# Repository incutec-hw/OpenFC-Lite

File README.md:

# OpenFC-Lite

Open-source Betaflight flight controller built on the RP2354B — 6-layer, 30.5×30.5 mm mounting, 3S–6S input, microSD blackbox, analog OSD.

Motor outputs are signal-level lines that drive an external 4-in-1 ESC (e.g. OpenESC) over the 8-pin ESC connector — there are no onboard motor drivers. Barometer, integrated receiver, and onboard SPI blackbox flash are omitted by design; blackbox logging uses the microSD slot, and the receiver connects externally over UART.

> A smaller **[OpenFC-Lite-Mini](https://github.com/incutec-hw/OpenFC-Lite-Mini)** (20×20 mm, RP2354A) shares this design. **Both are being ordered for Rev 2;** this full-size board adds bigger pads, more I/O, full-size SD, and OSD debug pads.

## Specifications

| | |
|---|---|
| **MCU** | RP2354B — dual-core ARM Cortex-M33, QFN-80, integrated stacked flash (U2, LCSC C39843328) |
| **IMU** | 6-axis MEMS on SPI0, LGA-14 footprint. Rev 1 populates LSM6DSV16XTR (U9). The footprint also accepts TDK ICM-426xx/456xx — IMU is a population choice, not a layout change |
| **Barometer** | None (omitted by design) |
| **Blackbox** | microSD card slot (push-push, TF-021B-H265 family) on SPI1 |
| **OSD** | Analog, PIO-driven: sync-separator comparator + video op-amp + SPDT analog switch (no MAX7456-class OSD chip, no onboard flash). Includes OSD debug/bring-up pads (not on the Mini). |
| **Regulators** | 10V switchable buck, 5V always-on buck, USB/BATT power mux, 3.3V LDO, 1.8V gyro LDO (see power tree) |
| **UARTs** | 4 total — 2 hardware UARTs + 2 PIO software UARTs |
| **Motor outputs** | 4 (MOTOR1–MOTOR4), signal-level to external ESC |
| **Battery input** | +BATT, 3S–6S |
| **Copper layers** | 6 |
| **Board size** | 38.9 × 38.9 mm |
| **Mounting** | 30.5 × 30.5 mm pattern, 4× Ø4.0 mm holes |
| **USB** | USB-C (USB full-speed, D+/D- with 30Ω series resistors; configuration/flashing) |

### Power tree

| Rail | Source | Regulator | Notes |
|---|---|---|---|
| +10V (switchable) | +BATT | LMR51430YFDDCR buck (U3) | EN-gated via GPIO (10V_ENABLE). FB divider 100k : 6.49k → ≈9.85V. 4.7µH (L2) / 22µF 16V output. VTX/camera rail. |
| +5V (always-on) | +BATT | LMR51430YFDDCR buck (U4) | 4.7µH (L3). |
| +5V (muxed) | +5V_BUCK + +5V_USB | TPS2116DRLR (U5) | Auto-selects battery vs USB source. |
| +3.3V | +5V | LP5912-3.3DRVR (U7) | Logic LDO. |
| +1.8V_GYRO | +5V | NCV8187AMT180TAG (U6) | 1.2 A LDO, high PSRR (80 dB to 10 kHz). Dedicated IMU analog supply. |
| +1.1V | +3.3V | RP2354B internal core regulator | MCU core. |

## Connectivity / IO

**Serial**
- UART0 (UART0_TX / UART0_RX) — hardware UART
- UART1 (UART1_TX / UART1_RX) — hardware UART
- PIO UART0 (PIOUART0_TX / PIOUART0_RX) — software UART via PIO
- PIO UART1 (PIOUART1_TX / PIOUART1_RX) — software UART via PIO

**Buses**
- I2C0 (SCL / SDA) — exposed on expansion pads
- SPI0 (SCK / MOSI / MISO, + GYRO_INT) — IMU
- SPI1 (SCK / MOSI / MISO) — microSD blackbox

**Motor / actuator**
- MOTOR1, MOTOR2, MOTOR3, MOTOR4 — to external ESC
- LED_STRIP — addressable LED output
- BEEPER / BUZZER- — N-MOS-driven buzzer output

**Analog inputs (each via RC filter)**
- ADC_VBAT — battery voltage sense (resistive divider)
- ESC_CURRENT — current sense from ESC
- RSSI — analog RSSI

**OSD (analog video chain)**
- OSD_SYNC, OSD_EN, OSD_W, OSD_LVL — composite-video sync/overlay signals to the OSD front-end

**Status / control**
- LED0 — status LED
- 10V_ENABLE — switches the 10V VTX/camera rail

### Connectors

| Ref | Part | Type | Function |
|---|---|---|---|
| U8 | SM06B-SRSS-TB | 6-pin SMD JST SH | Digital VTX |
| P1 | SM08B-SRSS-TB | 8-pin TH JST SH | ESC harness |
| USB1 | Type-C 16P | USB-C | Configuration / flashing |

A large number of through-hole solder pads (J*) expose rails and signal lines (5V, GND, MOTOR1–4, UART, LED_STRIP, RSSI, etc.) for direct wiring.

## Repository structure

```
OpenFC-Lite/
├── README.md
├── LICENSE                       CERN-OHL-S-2.0
├── CLAUDE.md                     project working agreement / design notes
├── hardware/                     KiCad 9 project (single project)
│   ├── OpenFC.kicad_pro          project file
│   ├── OpenFC.kicad_sch          top-level (hierarchical) schematic
│   ├── rp2350a.kicad_sch         RP2354B MCU + support
│   ├── power.kicad_sch           regulators (10V/5V bucks, mux, 3.3V/1.8V LDOs)
│   ├── imu.kicad_sch             6-axis IMU on SPI0
│   ├── osd.kicad_sch             analog OSD chain
│   ├── blackbox.kicad_sch        microSD card slot on SPI1
│   ├── pads.kicad_sch            solder pads and connectors
│   ├── OpenFC.kicad_pcb          PCB layout (6 layers)
│   ├── OpenFC.kicad_dru          custom design rules
│   ├── lib.kicad_sym             project-local symbol library
│   ├── lib.3dshapes/             project-local 3D models
│   ├── datasheets/               component datasheets
│   ├── production/               JLCPCB exports (rev1: gerbers zip, BOM, CPL)
│   └── tools/                    read-only analysis scripts (kicad-skip / pcbnew)
├── analysis/                     netlist/IC/power extraction output
└── images/                       board renders
```

All symbol, footprint, and 3D-model libraries are project-local — no external library setup required to open the project.

## Firmware

Target firmware is **Betaflight** on the RP2350 (PICO) platform. The RP2354B uses the Raspberry Pi Pico SDK (C/C++). PIO blocks drive the DShot motor outputs, the software UARTs, the LED strip, and the analog-OSD pixel timing.

Note: the RP2350 analog-OSD (FB_OSD) driver is still an open upstream Betaflight PR stack — OSD is not yet flyable from an upstream binary. See the [Wiki](https://github.com/incutec-hw/OpenFC-Lite/wiki) for bring-up status.

## License

Hardware licensed under [CERN-OHL-S-2.0](https://ohwr.org/cern_ohl_s_v2.txt). See [LICENSE](LICENSE).

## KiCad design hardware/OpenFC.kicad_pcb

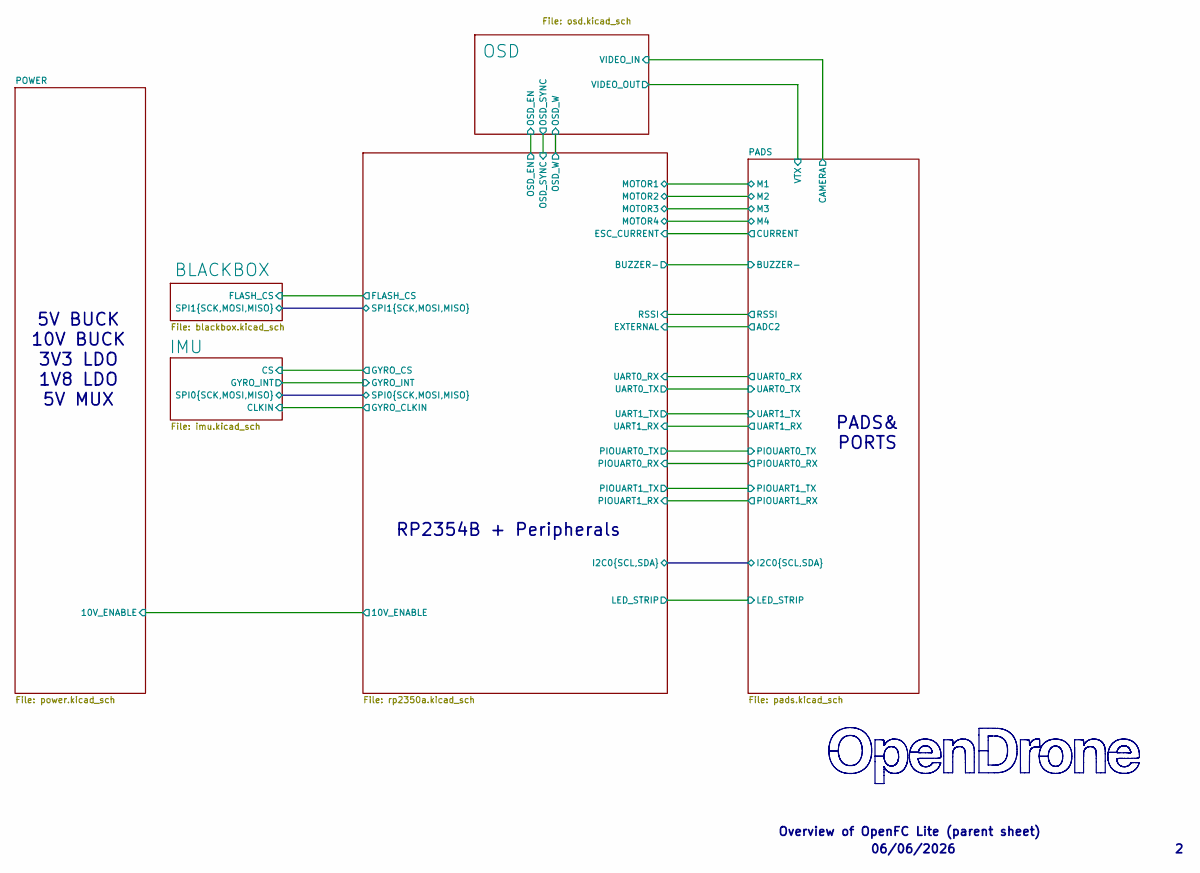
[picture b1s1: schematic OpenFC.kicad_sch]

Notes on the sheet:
Overview of OpenFC Lite (parent sheet)
5V BUCK 10V BUCK 3V3 LDO 1V8 LDO 5V MUX
06/06/2026
RP2354B + Peripherals
PADS& PORTS

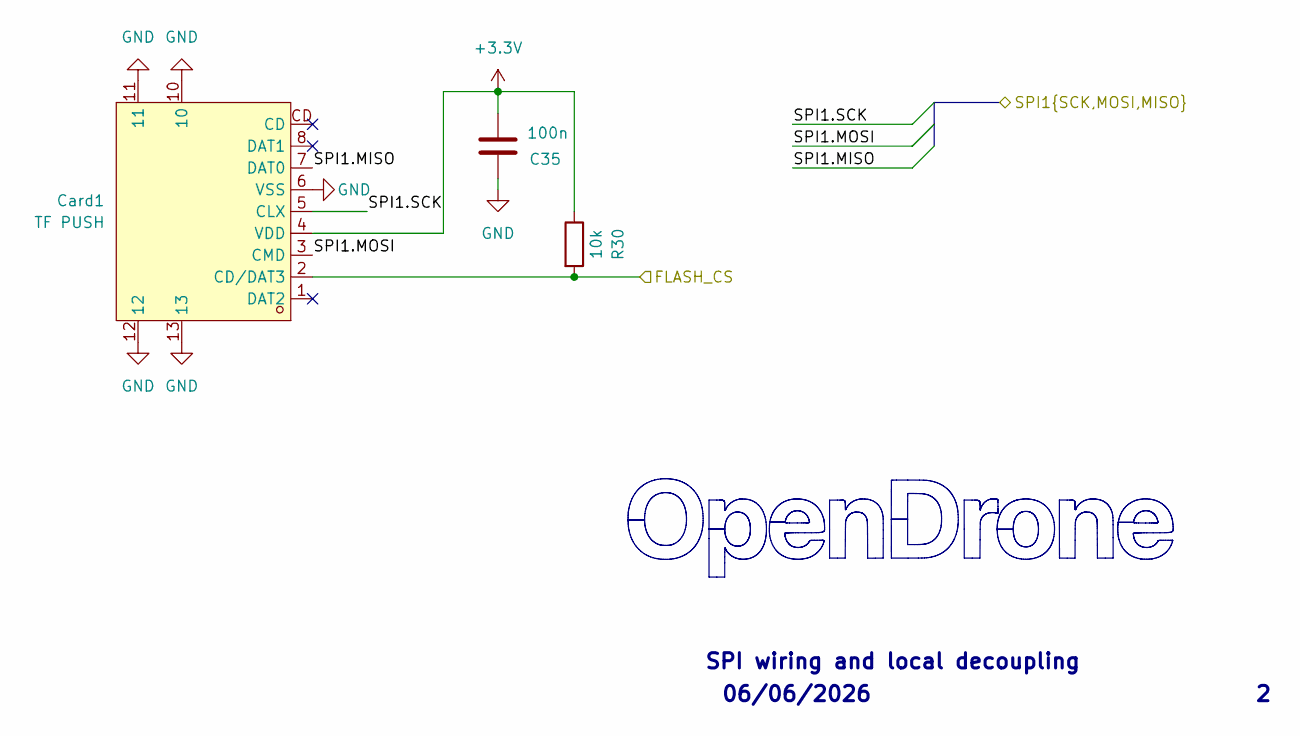
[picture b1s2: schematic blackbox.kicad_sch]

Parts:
C35: 100n; C_0201_0603Metric; MPN GRM033R61E104KE14D; LCSC C76939
Card1: TF PUSH; TF-SMD_TF-PUSH; MPN TF PUSH; LCSC C393941
R30: 10k; R_0201_0603Metric; MPN RC0201FR-0710KL; LCSC C106225

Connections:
+3.3V: C35.1, Card1.4 (VDD), R30.1; also elsewhere on the board
/BLACKBOX/FLASH_CS: Card1.2 (CD/DAT3), R30.2; also elsewhere on the board
/BLACKBOX/SPI1.MISO: Card1.7 (DAT0); also elsewhere on the board
/BLACKBOX/SPI1.MOSI: Card1.3 (CMD); also elsewhere on the board
/BLACKBOX/SPI1.SCK: Card1.5 (CLX); also elsewhere on the board
GND: C35.2, Card1.6 (VSS), Card1.10, Card1.11, Card1.12, Card1.13; also elsewhere on the board

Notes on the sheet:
SPI wiring and local decoupling
06/06/2026

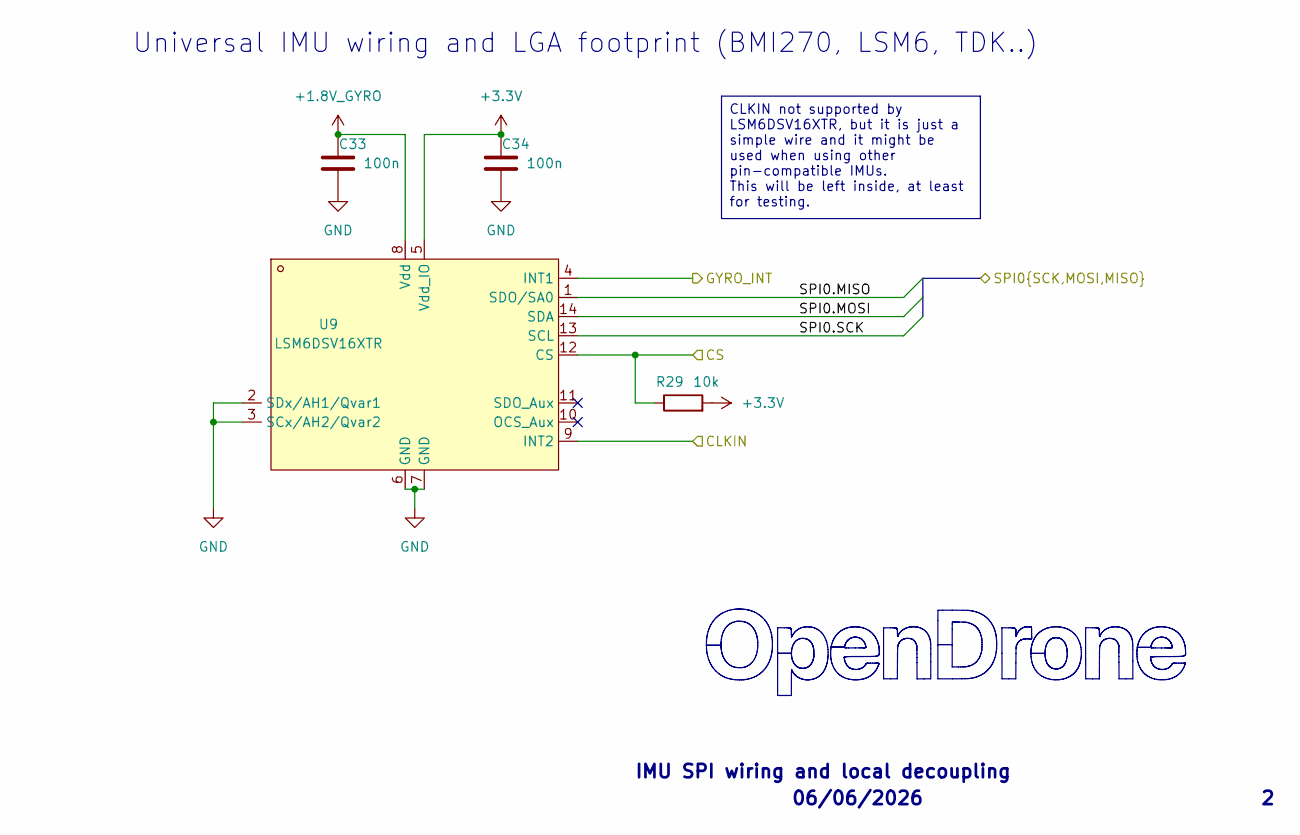
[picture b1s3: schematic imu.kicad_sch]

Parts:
C33, C34: 100n; C_0201_0603Metric; MPN GRM033R61E104KE14D; LCSC C76939
R29: 10k; R_0201_0603Metric; MPN RC0201FR-0710KL; LCSC C106225
U9: LSM6DSV16XTR; LGA-14_L3.0-W2.5-P0.50-BR; MPN LSM6DSV16XTR; LCSC C5267406

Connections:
+1.8V_GYRO: C33.1, U9.8 (Vdd); also elsewhere on the board
+3.3V: C34.1, R29.2, U9.5 (Vdd_IO); also elsewhere on the board
/IMU/CLKIN: U9.9 (INT2); also elsewhere on the board
/IMU/CS: R29.1, U9.12 (CS); also elsewhere on the board
/IMU/GYRO_INT: U9.4 (INT1); also elsewhere on the board
/IMU/SPI0.MISO: U9.1 (SDO/SA0); also elsewhere on the board
/IMU/SPI0.MOSI: U9.14 (SDA); also elsewhere on the board
/IMU/SPI0.SCK: U9.13 (SCL); also elsewhere on the board
GND: C33.2, C34.2, U9.2 (SDx/AH1/Qvar1), U9.3 (SCx/AH2/Qvar2), U9.6 (GND), U9.7 (GND); also elsewhere on the board

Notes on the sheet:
06/06/2026
IMU SPI wiring and local decoupling
Universal IMU wiring and LGA footprint (BMI270, LSM6, TDK..)
CLKIN not supported by LSM6DSV16XTR, but it is just a simple wire and it might be used when using other pin-compatible IMUs. This will be left inside, at least for testing.

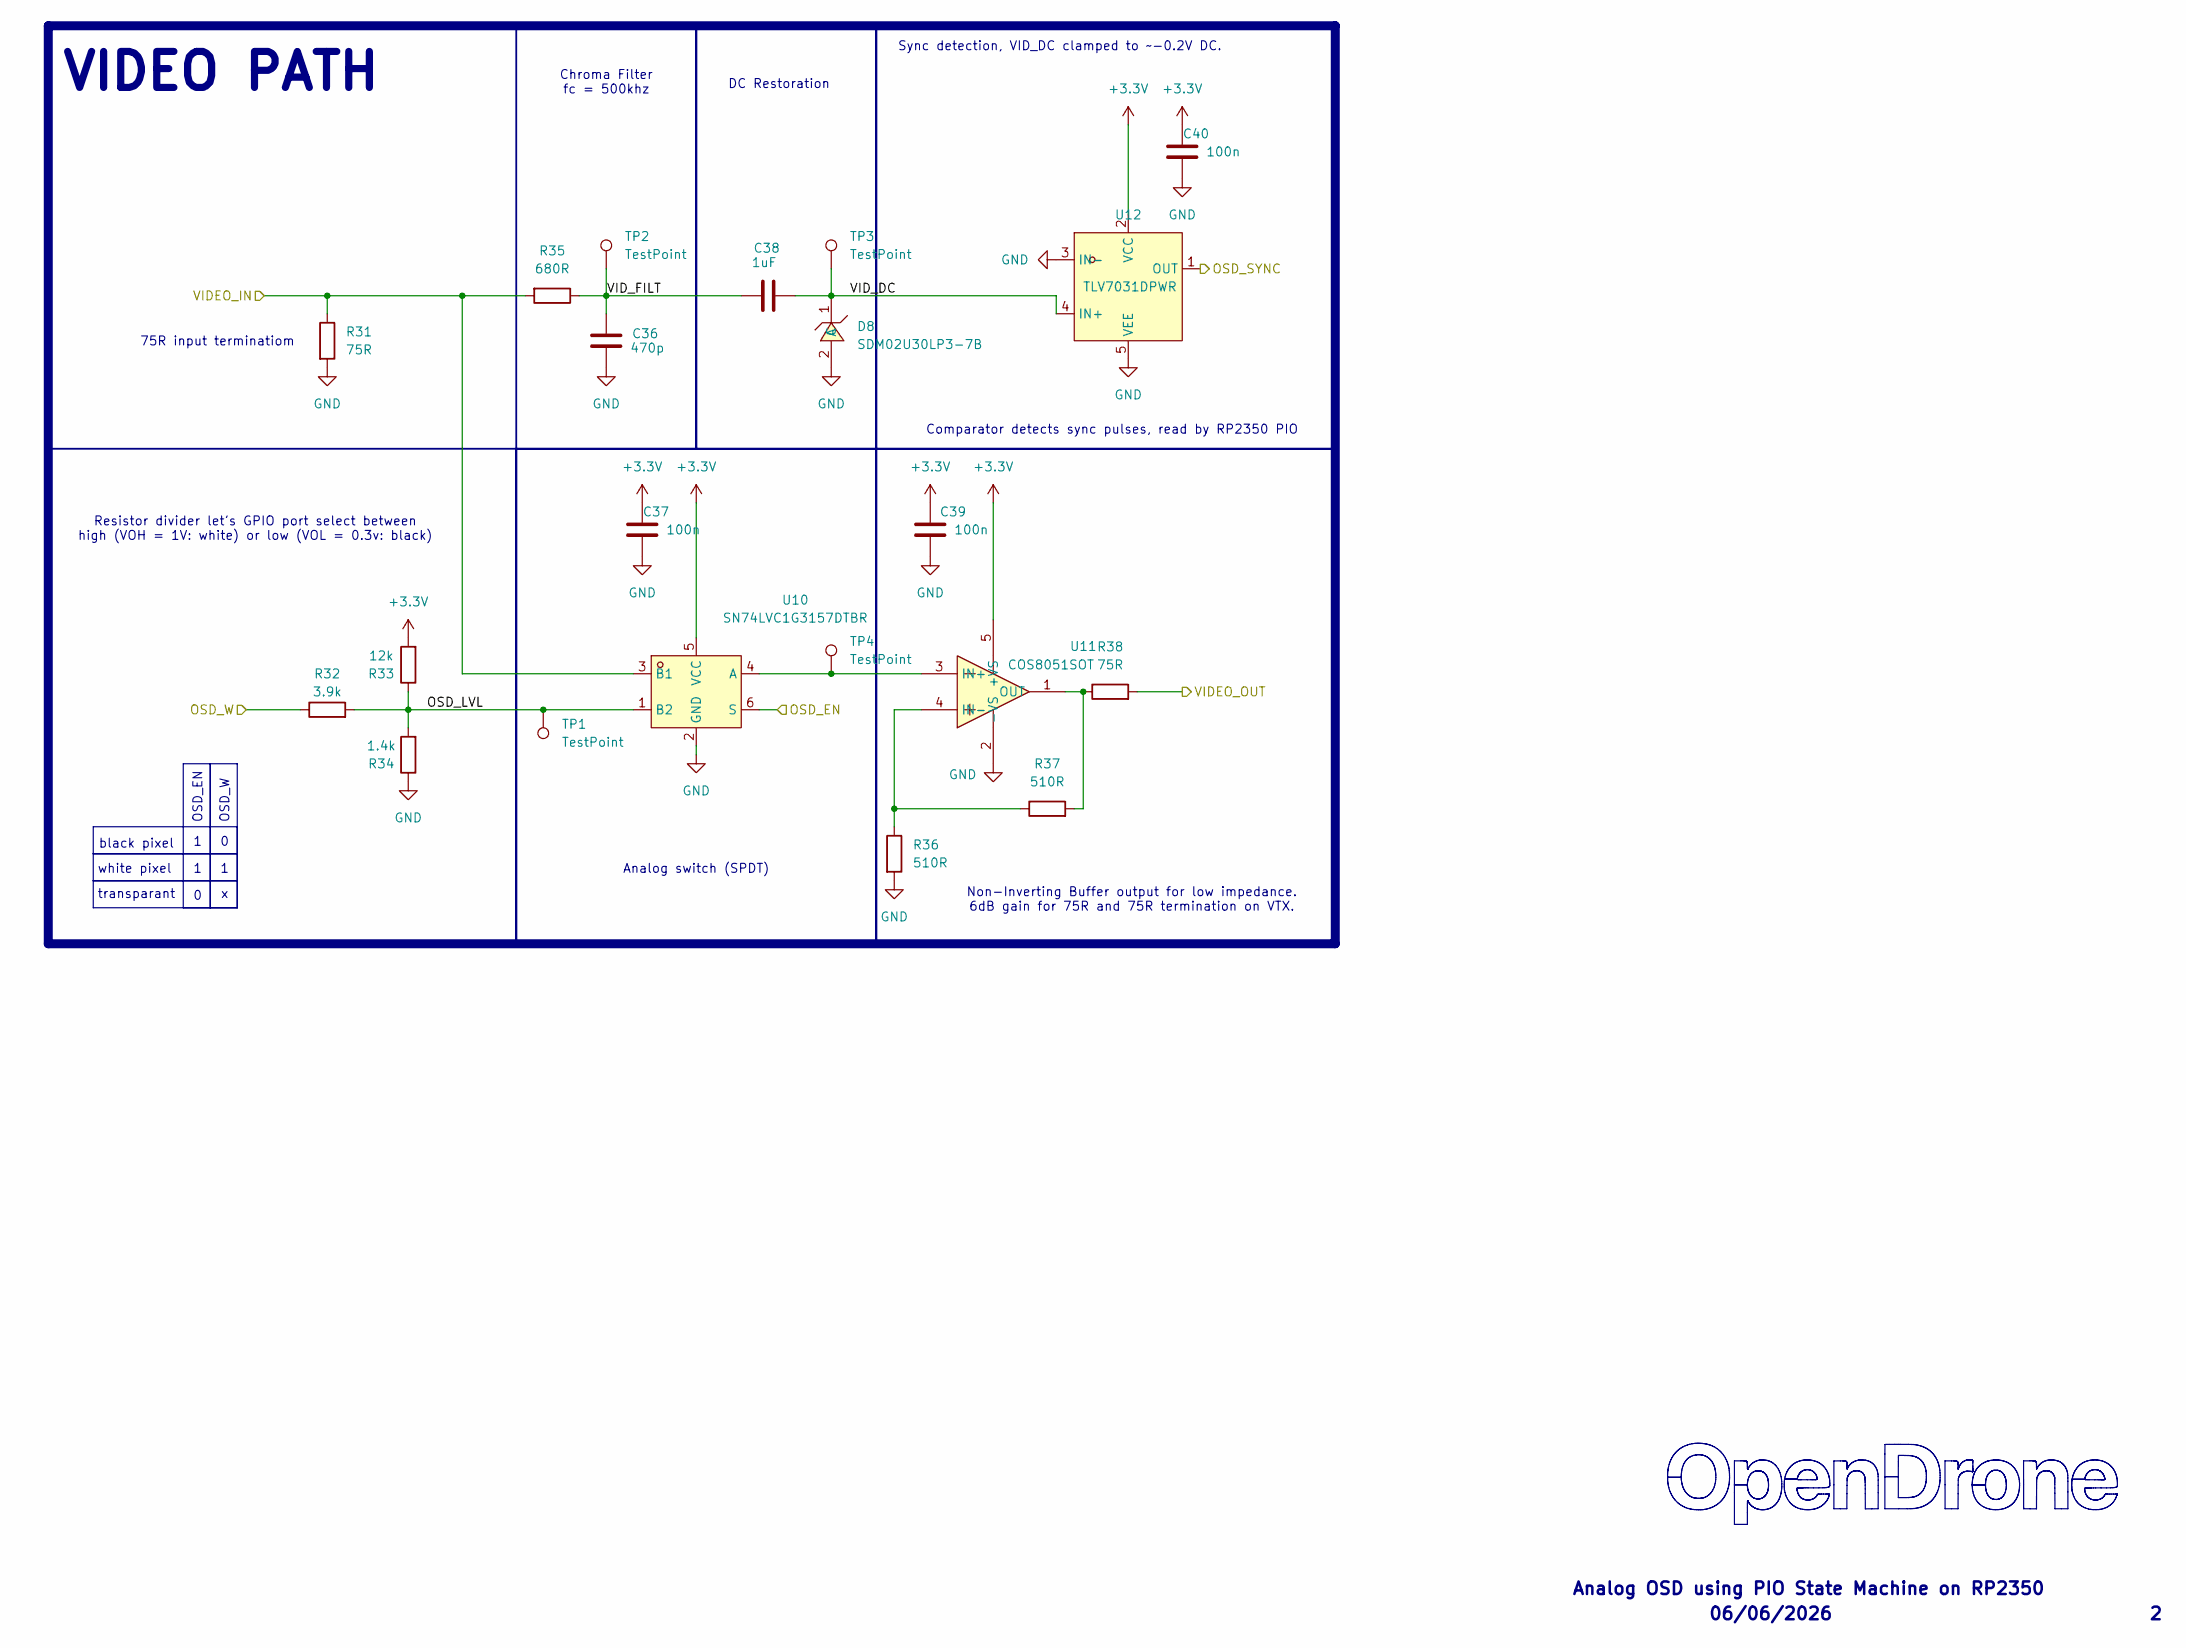
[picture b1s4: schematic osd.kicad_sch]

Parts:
C36: 470p; C_0201_0603Metric; MPN CC0201JRX7R9BB471; LCSC C526944
C37, C39, C40: 100n; C_0201_0603Metric; MPN GRM033R60J104KE19D; LCSC C76928
C38: 1uF; C_0402_1005Metric; MPN CL05A105KA5NQNC; LCSC C52923
D8: SDM02U30LP3-7B; X3-DFN0603-2_L0.6-W0.3-RD; MPN SDM02U30LP3-7B; LCSC C151629
R31, R38: 75R; R_0201_0603Metric; MPN RC0201FR-0775RL; LCSC C274878
R32: 3.9k; R_0201_0603Metric; MPN RC0201FR-073K9L; LCSC C273280
R33: 12k; R_0201_0603Metric; MPN 0201WMF1202TEE; LCSC C270363
R34: 1.4k; R_0201_0603Metric; MPN 0201WMF1401TEE; LCSC C423739
R35: 680R; R_0201_0603Metric; MPN 0201WMF6800TEE; LCSC C473509
R36, R37: 510R; R_0201_0603Metric; LCSC C57784
TP1, TP2, TP3, TP4: TestPoint; TestPoint_Pad_D1.5mm
U10: SN74LVC1G3157DTBR; X2SON-6_L1.0-W0.8-BL; MPN SN74LVC1G3157DTBR; LCSC C2673087
U11: COS8051SOT; SOT-23-5_L3.0-W1.7-P0.95-LS2.8-BR; MPN COS8051SOT; LCSC C7463385
U12: TLV7031DPWR; X2SON-4_L0.8-W0.8-P0.48-TL-A; MPN TLV7031DPWR; LCSC C2876045

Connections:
+3.3V: C37.1, C39.1, C40.1, R33.2, U10.5 (VCC), U11.5 (+VS), U12.2 (VCC); also elsewhere on the board
/OSD/OSD_EN: U10.6 (S); also elsewhere on the board
/OSD/OSD_LVL: R32.2, R33.1, R34.2, TP1.1 (1_1), U10.1 (B2)
/OSD/OSD_SYNC: U12.1 (OUT); also elsewhere on the board
/OSD/OSD_W: R32.1; also elsewhere on the board
/OSD/VIDEO_IN: R31.1, R35.2, U10.3 (B1); also elsewhere on the board
/OSD/VIDEO_OUT: R38.2; also elsewhere on the board
/OSD/VID_DC: C38.2, D8.1 (C), TP3.1 (1_1), U12.4 (IN+)
/OSD/VID_FILT: C36.1, C38.1, R35.1, TP2.1 (1_1)
GND: C36.2, C37.2, C39.2, C40.2, D8.2 (A), R31.2, R34.1, R36.2, U10.2 (GND), U11.2 (-VS), U12.3 (IN-), U12.5 (VEE); also elsewhere on the board
unnamed: TP4.1 (1_1), U10.4 (A), U11.3 (IN+)
unnamed: R36.1, R37.1, U11.4 (IN-)
unnamed: R37.2, R38.1, U11.1 (OUT)

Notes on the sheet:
black pixel
Comparator detects sync pulses, read by RP2350 PIO
06/06/2026
Analog OSD using PIO State Machine on RP2350
Sync detection, VID_DC clamped to ~-0.2V DC.
Non-Inverting Buffer output for low impedance. 6dB gain for 75R and 75R termination on VTX.
white pixel
75R input terminatiom
OSD_W
Chroma Filter fc = 500khz
VIDEO PATH
Analog switch (SPDT)
OSD_EN
transparant
DC Restoration
Resistor divider let's GPIO port select between high (VOH = 1V: white) or low (VOL = 0.3v: black)

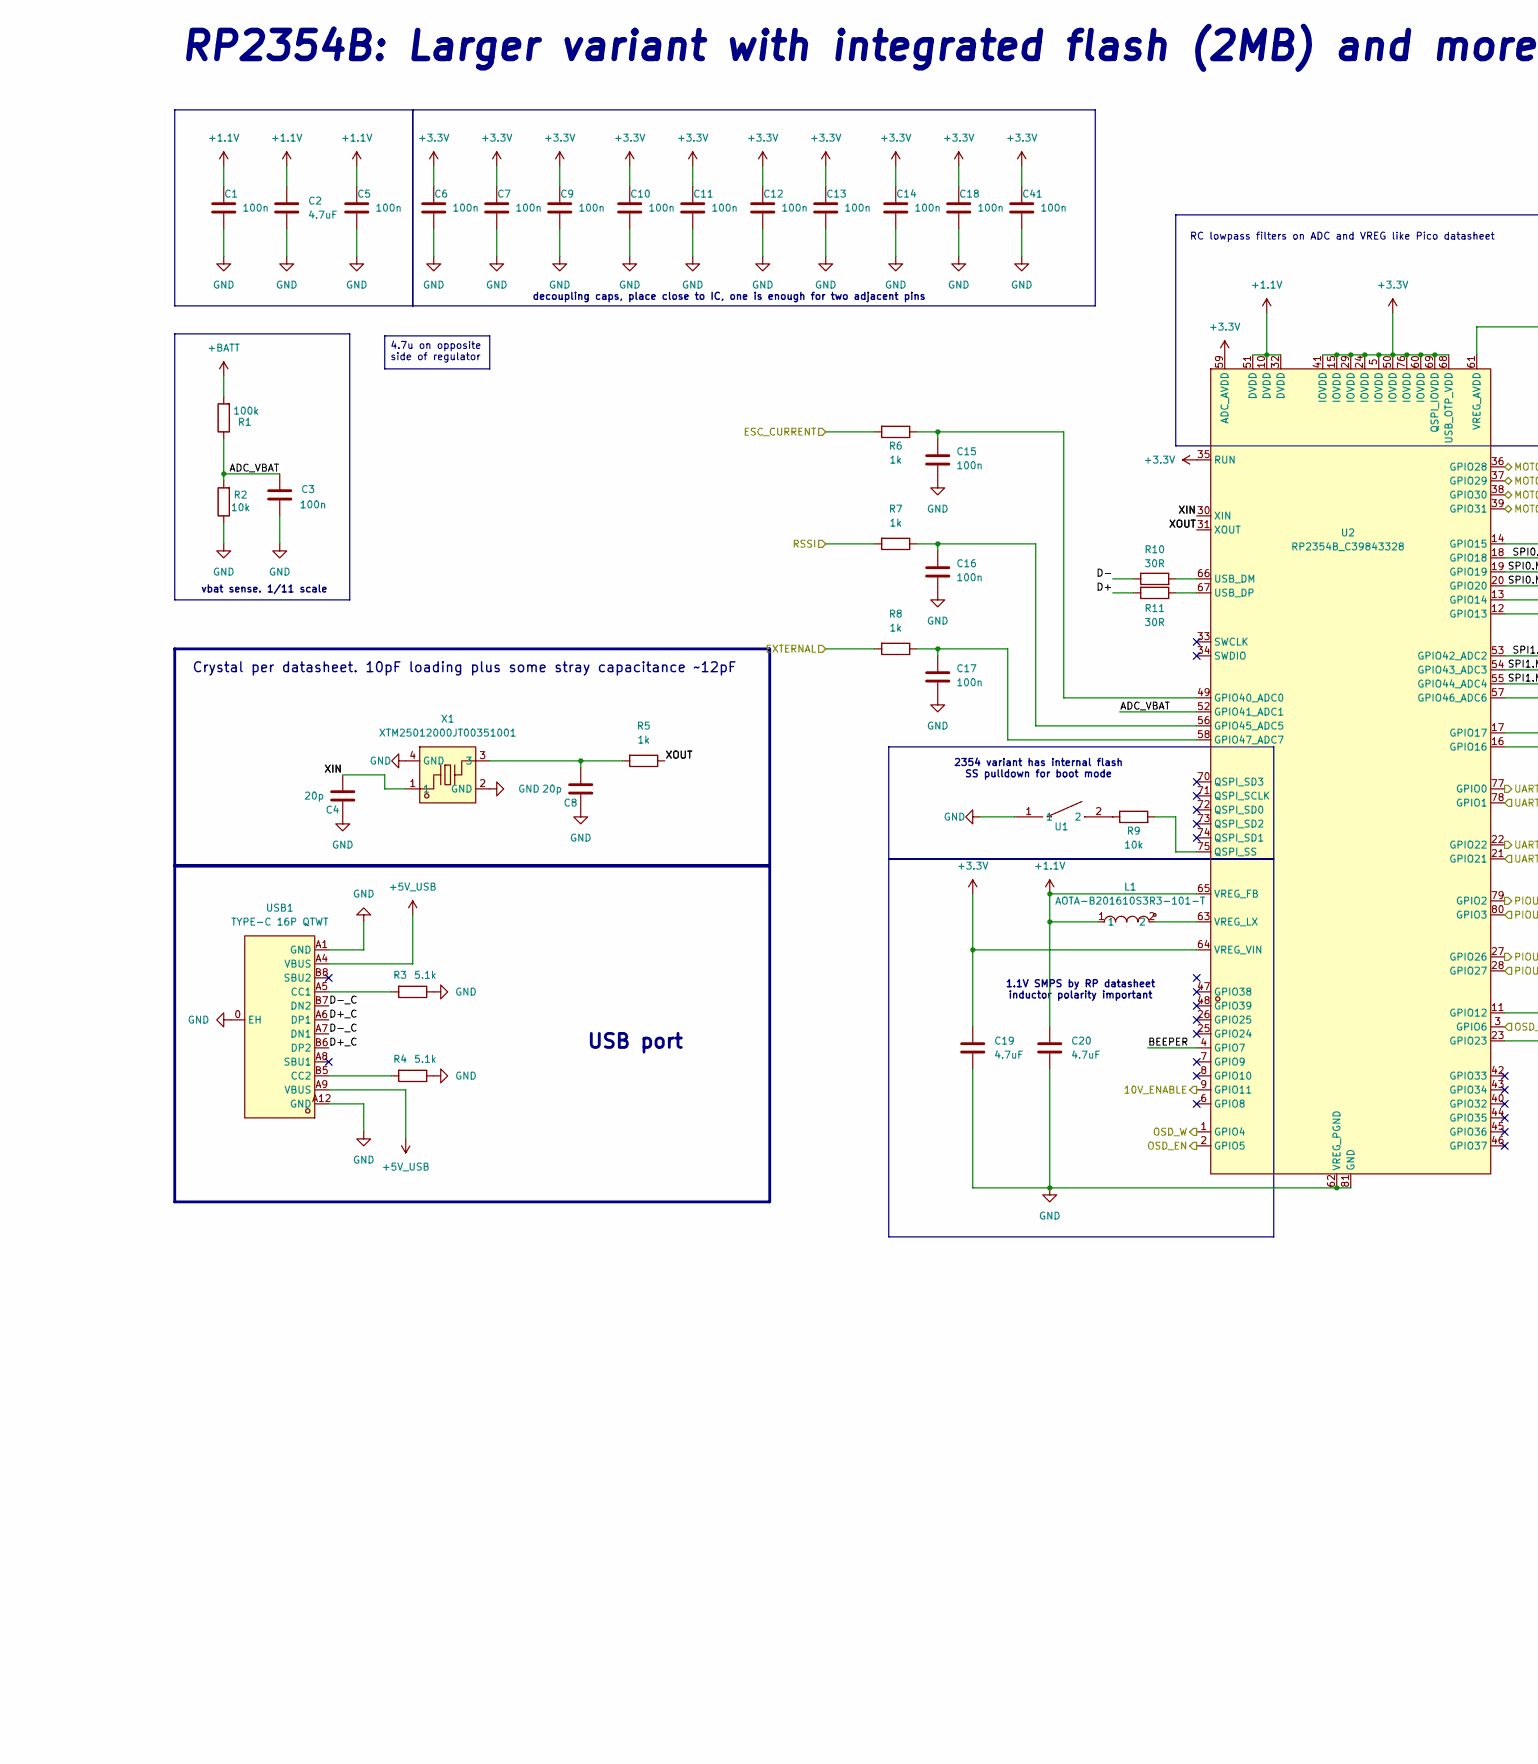
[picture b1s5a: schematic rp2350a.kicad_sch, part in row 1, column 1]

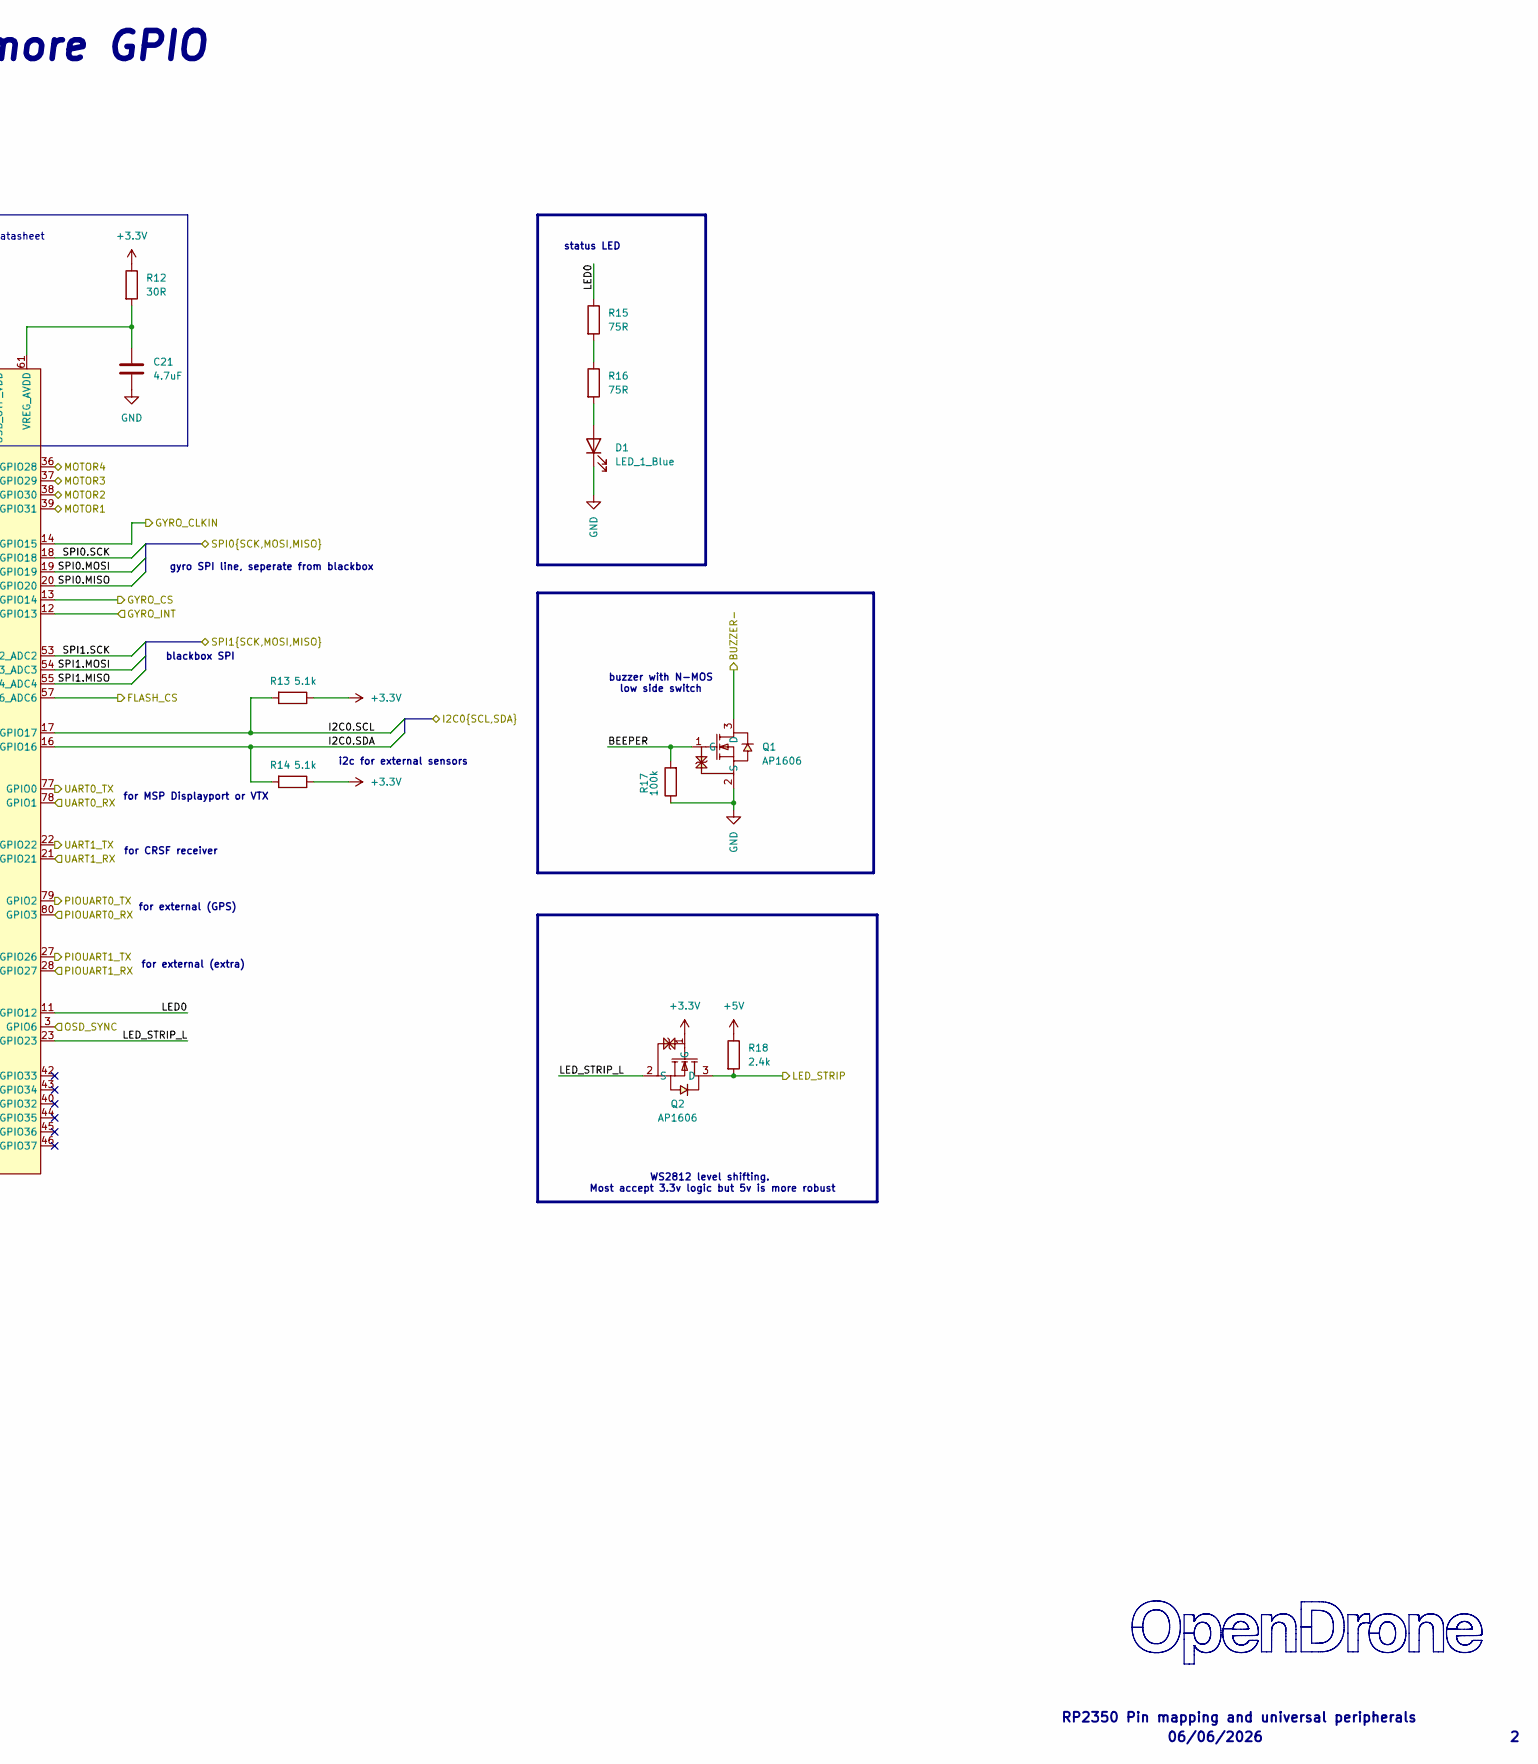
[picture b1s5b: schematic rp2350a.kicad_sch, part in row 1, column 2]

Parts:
C1, C3, C5, C6, C7, C9, C10, C11, C12, C13, C14, C15, C16, C17, C18, C41: 100n; C_0201_0603Metric; MPN GRM033R61E104KE14D; LCSC C76939
C2, C19, C20, C21: 4.7uF; C_0402_1005Metric; MPN CL05A475MP5NRNC; LCSC C23733
C4, C8: 20p; C_0201_0603Metric; MPN GRM0335C1H200JA01D; LCSC C76923
D1: LED_1_Blue; LED_0402_1005Metric; MPN XL-1005UBC; LCSC C22355736
L1: AOTA-B201610S3R3-101-T; IND-SMD_L2.0-W1.6_AOTA-B201610S3R3-101-T; MPN AOTA-B201610S3R3-101-T; LCSC C42411119
Q1, Q2: AP1606; DFN-3L_L1.0-W0.6-P0.65-BR; MPN AP1606; LCSC C2849580
R1, R17: 100k; R_0201_0603Metric; MPN 0201WMF1003TEE; LCSC C270364
R2, R9: 10k; R_0201_0603Metric; MPN RC0201FR-0710KL; LCSC C106225
R3, R4, R13, R14: 5.1k; R_0201_0603Metric; MPN 0201WMF5101TEE; LCSC C270344
R5, R6, R7, R8: 1k; R_0201_0603Metric; MPN 0201WMF1001TEE; LCSC C270365
R10, R11, R12: 30R; R_0201_0603Metric; MPN NQ01WMJ0300TEE; LCSC C778391
R15, R16: 75R; R_0201_0603Metric; MPN RC0201FR-0775RL; LCSC C274878
R18: 2.4k; R_0201_0603Metric; LCSC C166281
U1: TS2306A 240GF MSM 9_C2976675; SW-SMD_4P-L3.0-W2.0-P0.85-LS3.5; MPN TS2306A 240gf MSM 9; LCSC C2976675
U2: RP2354B_C39843328; QFN-80_L10.0-W10.0-P0.40-TL-EP3.4; MPN RP2354B; LCSC C39843328
USB1: TYPE-C 16P QTWT; USB-TYPE-C-SMD_TYPE-C-16P-QTWT; MPN TYPE-C 16P QTWT; LCSC C5187472
X1: XTM25012000JT00351001; CRYSTAL-SMD_4P-L2.5-W2.0-BL-A; MPN XTM25012000JT00351001; LCSC C37635340

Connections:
+1.1V: C1.1, C2.1, C5.1, C20.1, L1.1, U2.10 (DVDD), U2.32 (DVDD), U2.51 (DVDD), U2.65 (VREG_FB)
+3.3V: C6.1, C7.1, C9.1, C10.1, C11.1, C12.1, C13.1, C14.1, C18.1, C19.1, C41.1, Q2.1 (G), R12.1, R13.1, R14.1, U2.5 (IOVDD), U2.15 (IOVDD), U2.24 (IOVDD), U2.29 (IOVDD), U2.35 (RUN), U2.41 (IOVDD), U2.50 (IOVDD), U2.59 (ADC_AVDD), U2.60 (IOVDD), U2.64 (VREG_VIN), U2.68 (USB_OTP_VDD), U2.69 (QSPI_IOVDD), U2.76 (IOVDD); also elsewhere on the board
+5V: R18.1; also elsewhere on the board
+5V_USB: USB1.A4 (VBUS), USB1.A9 (VBUS); also elsewhere on the board
+BATT: R1.2; also elsewhere on the board
/BLACKBOX/FLASH_CS: U2.57 (GPIO46_ADC6); also elsewhere on the board
/BLACKBOX/SPI1.MISO: U2.55 (GPIO44_ADC4); also elsewhere on the board
/BLACKBOX/SPI1.MOSI: U2.54 (GPIO43_ADC3); also elsewhere on the board
/BLACKBOX/SPI1.SCK: U2.53 (GPIO42_ADC2); also elsewhere on the board
/IMU/CLKIN: U2.14 (GPIO15); also elsewhere on the board
/IMU/CS: U2.13 (GPIO14); also elsewhere on the board
/IMU/GYRO_INT: U2.12 (GPIO13); also elsewhere on the board
/IMU/SPI0.MISO: U2.20 (GPIO20); also elsewhere on the board
/IMU/SPI0.MOSI: U2.19 (GPIO19); also elsewhere on the board
/IMU/SPI0.SCK: U2.18 (GPIO18); also elsewhere on the board
/OSD/OSD_EN: U2.2 (GPIO5); also elsewhere on the board
/OSD/OSD_SYNC: U2.3 (GPIO6); also elsewhere on the board
/OSD/OSD_W: U2.1 (GPIO4); also elsewhere on the board
/PADS/ADC2: R8.2; also elsewhere on the board
/PADS/BUZZER-: Q1.3 (D); also elsewhere on the board
/PADS/CURRENT: R6.2; also elsewhere on the board
/PADS/I2C0.SCL: R13.2, U2.17 (GPIO17); also elsewhere on the board
/PADS/I2C0.SDA: R14.2, U2.16 (GPIO16); also elsewhere on the board
/PADS/LED_STRIP: Q2.3 (D), R18.2; also elsewhere on the board
/PADS/M1: U2.39 (GPIO31); also elsewhere on the board
/PADS/M2: U2.38 (GPIO30); also elsewhere on the board
/PADS/M3: U2.37 (GPIO29); also elsewhere on the board
/PADS/M4: U2.36 (GPIO28); also elsewhere on the board
/PADS/PIOUART0_RX: U2.80 (GPIO3); also elsewhere on the board
/PADS/PIOUART0_TX: U2.79 (GPIO2); also elsewhere on the board
/PADS/PIOUART1_TX: U2.27 (GPIO26); also elsewhere on the board
/PADS/PU1RX: U2.28 (GPIO27); also elsewhere on the board
/PADS/RSSI: R7.2; also elsewhere on the board
/PADS/U1RX: U2.21 (GPIO21); also elsewhere on the board
/PADS/UART0_RX: U2.78 (GPIO1); also elsewhere on the board
/PADS/UART0_TX: U2.77 (GPIO0); also elsewhere on the board
/PADS/UART1_TX: U2.22 (GPIO22); also elsewhere on the board
/POWER/10V_ENABLE: U2.9 (GPIO11); also elsewhere on the board
/RP2350A/ADC_VBAT: C3.2, R1.1, R2.2, U2.52 (GPIO41_ADC1)
/RP2350A/BEEPER: Q1.1 (G), R17.2, U2.4 (GPIO7)
/RP2350A/D+: R11.2
/RP2350A/D+_C: USB1.A6 (DP1), USB1.B6 (DP2)
/RP2350A/D-: R10.1
/RP2350A/D-_C: USB1.A7 (DN1), USB1.B7 (DN2)
/RP2350A/LED0: R15.1, U2.11 (GPIO12)
/RP2350A/LED_STRIP_L: Q2.2 (S), U2.23 (GPIO23)
/RP2350A/XIN: C4.2, U2.30 (XIN), X1.1
/RP2350A/XOUT: R5.1, U2.31 (XOUT)
GND: C1.2, C2.2, C3.1, C4.1, C5.2, C6.2, C7.2, C8.1, C9.2, C10.2, C11.2, C12.2, C13.2, C14.2, C15.2, C16.2, C17.2, C18.2, C19.2, C20.2, C21.2, C41.2, D1.1 (K), Q1.2 (S), R2.1, R3.1, R4.1, R17.1, U1.1, U2.62 (VREG_PGND), U2.81 (GND), USB1.0 (EH), USB1.A1 (GND), USB1.A12 (GND), X1.2 (GND), X1.4 (GND); also elsewhere on the board
unnamed: C8.2, R5.2, X1.3
unnamed: D1.2 (A), R16.2
unnamed: R9.1, U1.2
unnamed: R15.2, R16.1
unnamed: C15.1, R6.1, U2.49 (GPIO40_ADC0)
unnamed: C16.1, R7.1, U2.56 (GPIO45_ADC5)
unnamed: C17.1, R8.1, U2.58 (GPIO47_ADC7)
unnamed: R9.2, U2.75 (QSPI_SS)
unnamed: R10.2, U2.66 (USB_DM)
unnamed: R11.1, U2.67 (USB_DP)
unnamed: C21.1, R12.2, U2.61 (VREG_AVDD)
unnamed: L1.2, U2.63 (VREG_LX)
unnamed: R3.2, USB1.A5 (CC1)
unnamed: R4.2, USB1.B5 (CC2)

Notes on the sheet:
RP2350 Pin mapping and universal peripherals
vbat sense. 1/11 scale
RP2354B: Larger variant with integrated flash (2MB) and more GPIO
blackbox SPI
06/06/2026
for MSP Displayport or VTX
2354 variant has internal flash SS pulldown for boot mode
for CRSF receiver
gyro SPI line, seperate from blackbox
decoupling caps, place close to IC, one is enough for two adjacent pins
for external (extra)
Crystal per datasheet. 10pF loading plus some stray capacitance ~12pF
for external (GPS)
i2c for external sensors
WS2812 level shifting. Most accept 3.3v logic but 5v is more robust
status LED
RC lowpass filters on ADC and VREG like Pico datasheet
USB port
1.1V SMPS by RP datasheet inductor polarity important
buzzer with N-MOS low side switch
4.7u on opposite side of regulator
